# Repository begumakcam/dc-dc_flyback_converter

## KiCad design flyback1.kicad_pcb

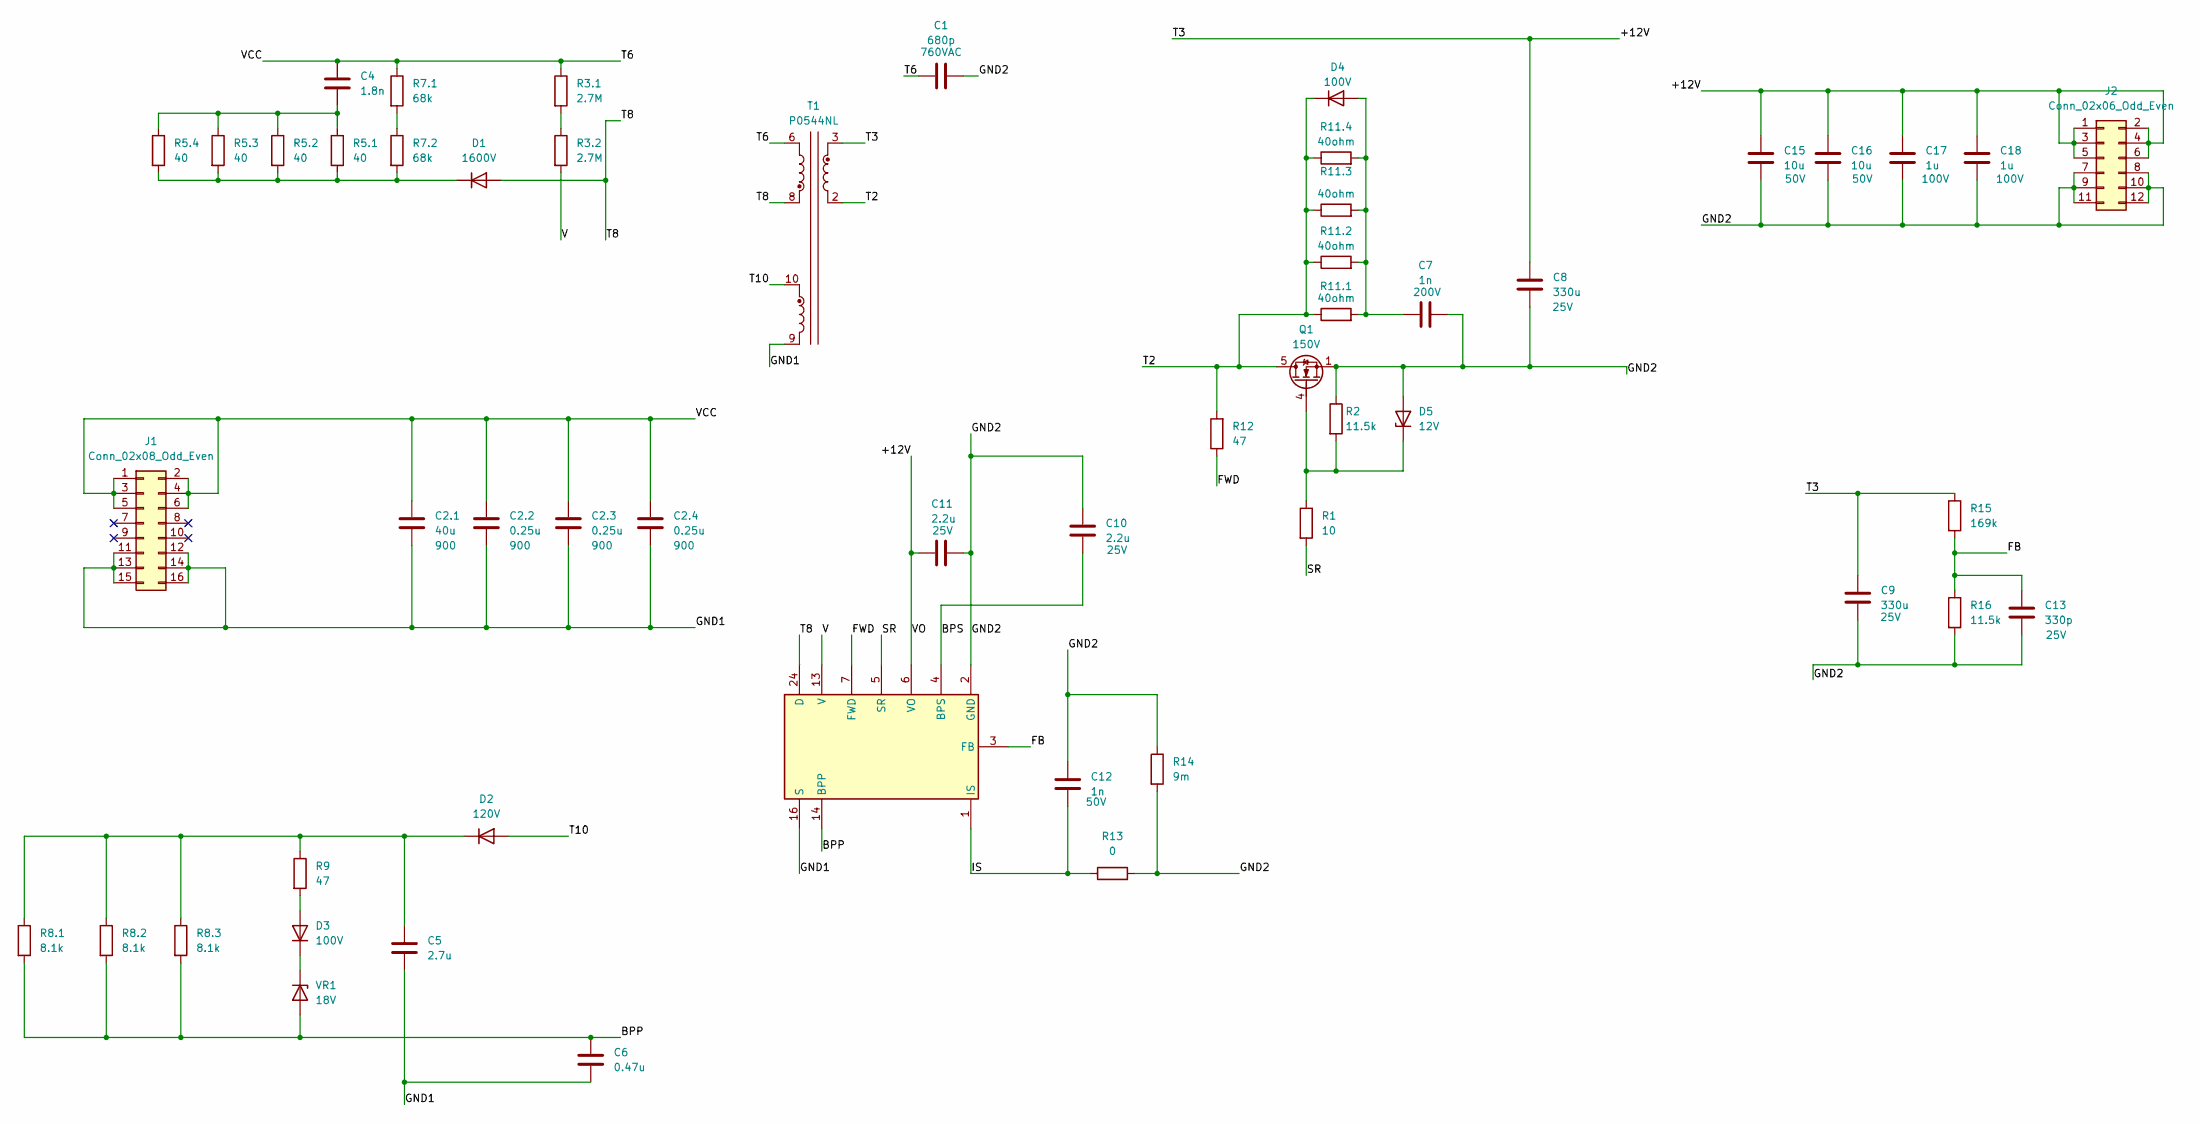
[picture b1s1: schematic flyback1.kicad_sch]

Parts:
C1: 680p; C_Disc_D8.0mm_W5.0mm_P10.00mm; VOLTAGE 760VAC
C2.1: 40u; C4AQNBW5400M3NJ; Voltage 900
C2.2: 0.25u; C_Disc_D8.0mm_W5.0mm_P10.00mm; Voltage 900
C2.3, C2.4: 0.25u; B58031U9254M062; Voltage 900
C4: 1.8n; C_1210_3225Metric_Pad1.33x2.70mm_HandSolder
C5: 2.7u; C_1210_3225Metric_Pad1.33x2.70mm_HandSolder
C6: 0.47u; C_1206_3216Metric_Pad1.33x1.80mm_HandSolder
C7: 1n; C_1206_3216Metric_Pad1.33x1.80mm_HandSolder; Voltage 200V
C8, C9: 330u; 16SVF1000M; Voltage 25V
C10, C11: 2.2u; C_0805_2012Metric_Pad1.18x1.45mm_HandSolder; Voltage 25V
C12: 1n; C_1206_3216Metric_Pad1.33x1.80mm_HandSolder; Voltage 50V
C13: 330p; C_1206_3216Metric_Pad1.33x1.80mm_HandSolder; Voltage 25V
C15, C16: 10u; C_1210_3225Metric_Pad1.33x2.70mm_HandSolder; Voltage 50V
C17, C18: 1u; C_0805_2012Metric_Pad1.18x1.45mm_HandSolder; Voltage 100V
D1: 1600V; DIOM5127X229N
D2: 120V; D_SMP_DO-220AA
D3, D4: 100V; SOD123_MCC
D5: 12V; SOD123_MCC
IC1: INN3649C-H606-TL; INN3649CH606TL; Manufacturer_Part_Number INN3649C-H606-TL; Mouser Part Number 869-INN3649C-H606-TL
J1: Conn_02x08_Odd_Even; PinSocket_2x08_P2.54mm_Vertical
J2: Conn_02x06_Odd_Even; PinSocket_2x06_P2.54mm_Vertical
Q1: 150V; TDSON-8-1
R1: 10; R_0603_1608Metric_Pad0.98x0.95mm_HandSolder
R2, R16: 11.5k; R_1206_3216Metric_Pad1.30x1.75mm_HandSolder
R3.1, R3.2: 2.7M; R_2512_6332Metric_Pad1.40x3.35mm_HandSolder
R5.1, R5.2, R5.3, R5.4: 40; R_1206_3216Metric_Pad1.30x1.75mm_HandSolder
R7.1, R7.2: 68k; R_2512_6332Metric_Pad1.40x3.35mm_HandSolder
R8.1, R8.2, R8.3: 8.1k; R_0805_2012Metric_Pad1.20x1.40mm_HandSolder
R9, R12: 47; R_0805_2012Metric_Pad1.20x1.40mm_HandSolder
R11.1, R11.2, R11.3, R11.4: 40ohm; R_1206_3216Metric_Pad1.30x1.75mm_HandSolder
R13: 0; R_1206_3216Metric_Pad1.30x1.75mm_HandSolder
R14: 9m; R_1206_3216Metric_Pad1.30x1.75mm_HandSolder
R15: 169k; R_0603_1608Metric_Pad0.98x0.95mm_HandSolder
T1: P0544NL; DIPS1016W120P380L2225H2324Q10N
VR1: 18V; SOD3716X135N

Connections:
/+12V: C8.2, C9.1, C11.1, C15.1, C16.1, C17.1, C18.1, IC1.6 (VO), J2.1, J2.2, J2.3, J2.4, J2.5, J2.6, R15.1, T1.3
/BPP: C6.1, IC1.14 (BPP), R8.1.2, R8.2.2, R8.3.2, VR1.2 (A)
/BPS: C10.2, IC1.4 (BPS)
/FB: C13.1, IC1.3 (FB), R15.2, R16.1
/FWD: IC1.7 (FWD), R12.1
/GND1: C2.1.2, C2.2.2, C2.3.2, C2.4.2, C5.2, C6.2, IC1.16 (S), J1.11, J1.12, J1.13, J1.14, J1.15, J1.16, T1.9
/GND2: C1.2, C7.2, C8.1, C9.2, C10.1, C11.2, C12.1, C13.2, C15.2, C16.2, C17.2, C18.2, D5.2 (A), IC1.2 (GND), J2.7, J2.8, J2.9, J2.10, J2.11, J2.12, Q1.1 (S), Q1.2 (S), Q1.3 (S), R2.1, R13.2, R14.1, R14.2, R16.2
/IS: C12.2, IC1.1 (IS), R13.1
/SR: IC1.5 (SR), R1.2
/T2: D4.1 (K), Q1.5 (D), R11.1.1, R11.2.1, R11.3.1, R11.4.1, R12.2, T1.2
/T6: C1.1, C2.1.1, C2.2.1, C2.3.1, C2.4.1, C4.2, J1.1, J1.2, J1.3, J1.4, J1.5, J1.6, R3.1.1, R7.1.1, T1.6
/T8: D1.2 (A), IC1.24 (D), T1.8
/T10: D2.2 (A), T1.10
/V: IC1.13 (V), R3.2.2
unnamed: C4.1, R5.1.1, R5.2.1, R5.3.1, R5.4.1
unnamed: D1.1 (K), R5.1.2, R5.2.2, R5.3.2, R5.4.2, R7.2.2
unnamed: C5.1, D2.1 (K), R8.1.1, R8.2.1, R8.3.1, R9.1
unnamed: D3.2 (A), R9.2
unnamed: D3.1 (K), VR1.1 (K)
unnamed: C7.1, D4.2 (A), R11.1.2, R11.2.2, R11.3.2, R11.4.2
unnamed: D5.1 (K), Q1.4 (G), R1.1, R2.2
unnamed: R3.1.2, R3.2.1
unnamed: R7.1.2, R7.2.1

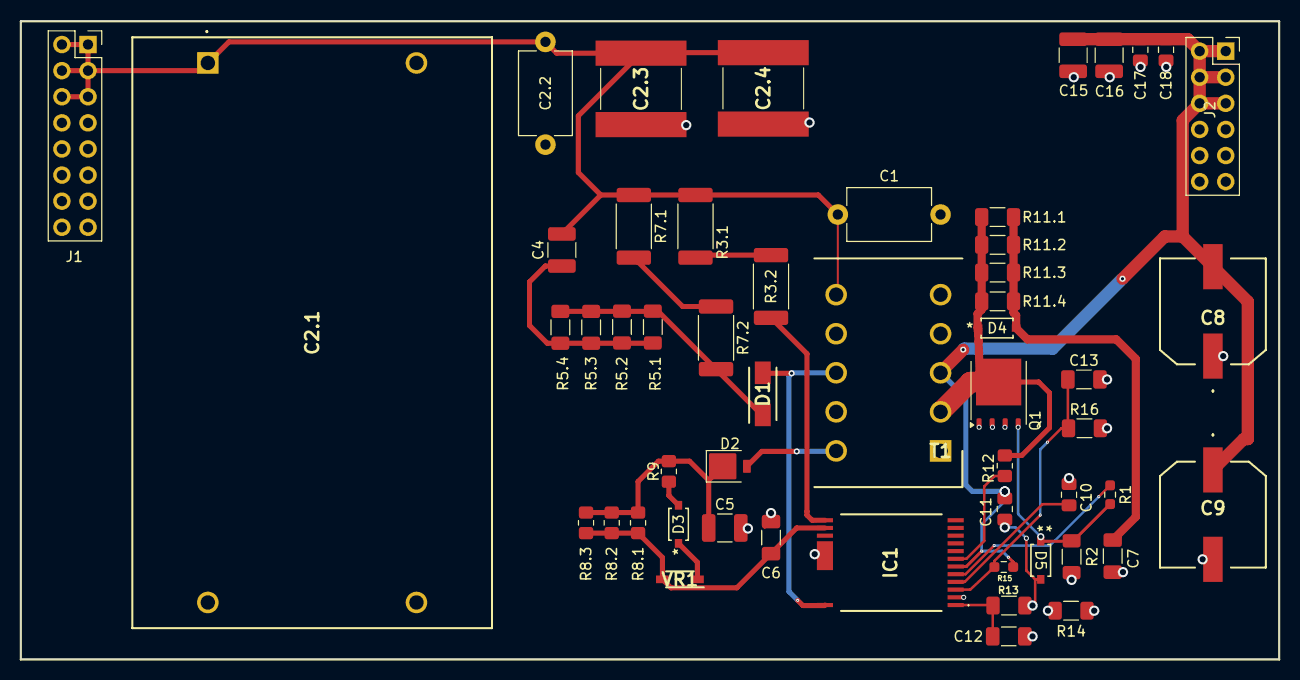
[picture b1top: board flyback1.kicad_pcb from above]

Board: 2 copper layers, 122.4 x 62.1 mm, 53 parts (0 on the bottom side), 23 nets.
